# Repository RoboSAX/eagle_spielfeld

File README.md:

# eagle_spielfeld
Masterplatine des Spielfeldes

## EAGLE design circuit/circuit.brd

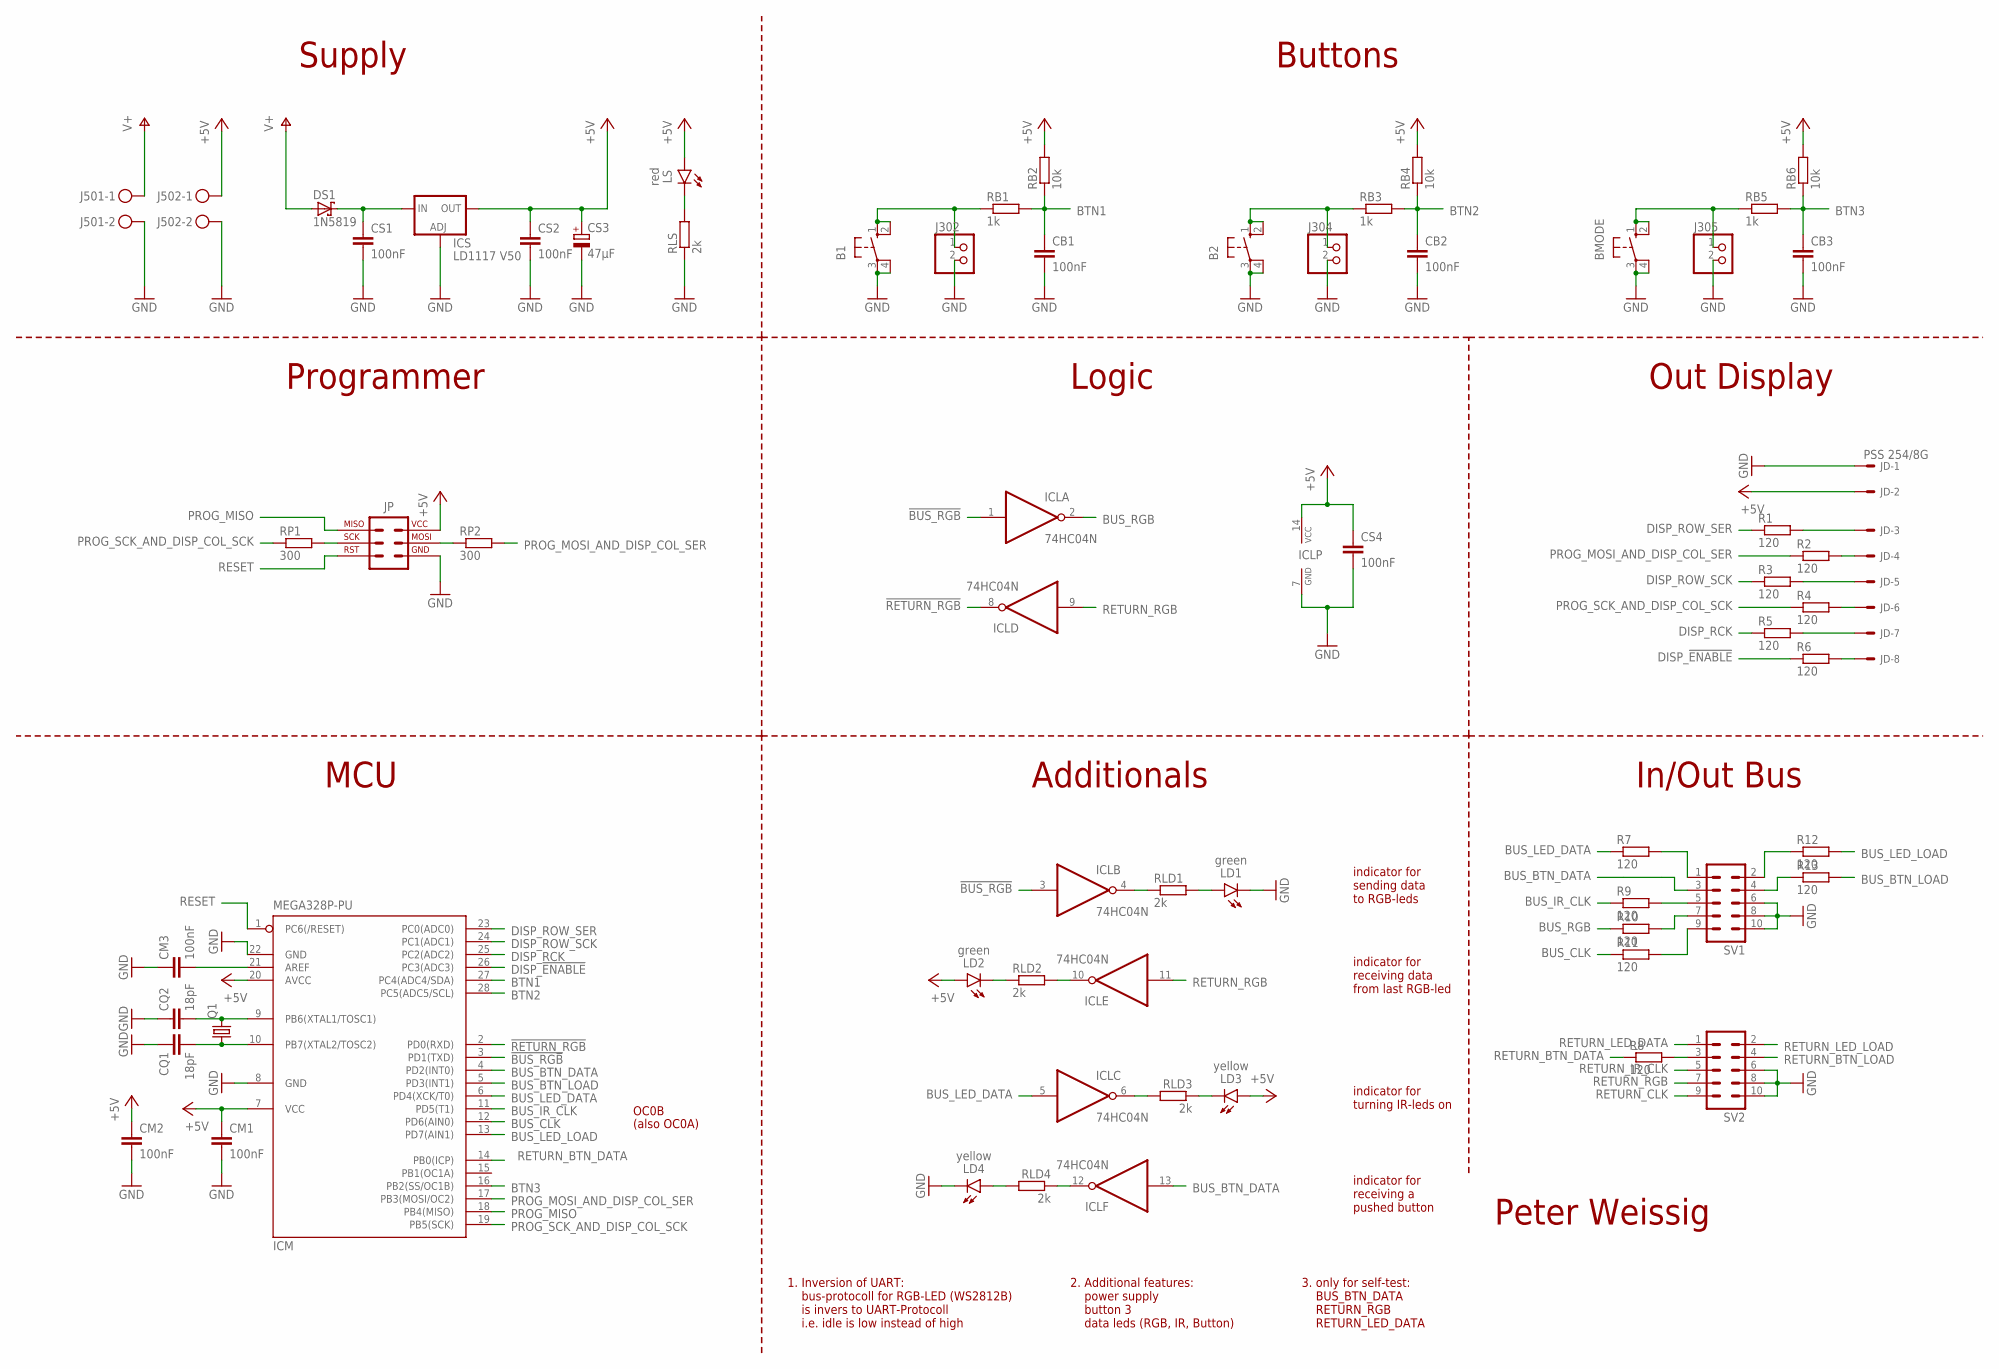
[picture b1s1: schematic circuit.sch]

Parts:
B1, B2: 10-XX; B3F-10XX
BMODE: 10-XX; B3F-10XX
CB1, CB2, CB3: 100nF; C025-025X050
CM1, CM2, CM3: 100nF; C025-025X050
CQ1, CQ2: 18pF; C025-025X050
CS1, CS2, CS4: 100nF; C025-025X050
CS3: 47µF; E2-5
DS1: 1N5819; DO41-7.6
ICL: 74HC04N; DIL14
ICM: MEGA328P-PU; DIL28-3
ICS: LD1117 V50; TO220L1
J302, J304, J305: PINHD-1X2; 1X02
J501, J502: STECKER_SPG_2
JD: PSS 254/8G; 22-23-2081
JP: STECKER_ISP_6; STECKER_WANNE_6
LD1, LD2: green; LED_3MM
LD3, LD4: yellow; LED_3MM
LS: red; LED_3MM
Q1: CRYSTALHC49U70; HC49U70
R1, R2, R3, R4, R5, R6, R7, R8, R9, R10, R11, R12, R13: 120; R1206W
RB1, RB3, RB5: 1k; 0207/10
RB2, RB4, RB6: 10k; 0207/10
RLD1, RLD2, RLD3, RLD4: 2k; 0207/10
RLS: 2k; 0207/10
RP1, RP2: 300; 0207/10
SV1, SV2: ML10

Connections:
!BUS_RGB: ICL.1 (I), ICL.3 (I), ICM.3 (PD1(TXD))
!RETURN_RGB: ICL.8 (O), ICM.2 (PD0(RXD))
+5V: CM1.1, CM2.1, CS2.1, CS3.+, CS4.1, ICL.14 (VCC), ICM.7 (VCC), ICM.20 (AVCC), ICS.2 (OUT), J502.1, JD.2, JP.2 (2_VCC), LD2.A, LD3.A, LS.A, RB2.2, RB4.2, RB6.2
BTN1: CB1.1, ICM.27 (PC4(ADC4/SDA)), RB1.2, RB2.1
BTN2: CB2.1, ICM.28 (PC5(ADC5/SCL)), RB3.2, RB4.1
BTN3: CB3.1, ICM.16 (PB2(SS/OC1B)), RB5.2, RB6.1
BUS_BTN_DATA: ICL.13 (I), ICM.4 (PD2(INT0)), SV1.3
BUS_BTN_LOAD: ICM.5 (PD3(INT1)), R13.2
BUS_CLK: ICM.12 (PD6(AIN0)), R11.1
BUS_IR_CLK: ICM.11 (PD5(T1)), R9.1
BUS_LED_DATA: ICL.5 (I), ICM.6 (PD4(XCK/T0)), R7.1
BUS_LED_LOAD: ICM.13 (PD7(AIN1)), R12.2
BUS_RGB: ICL.2 (O), R10.1
DISP_!ENABLE!: ICM.26 (PC3(ADC3)), R6.1
DISP_RCK: ICM.25 (PC2(ADC2)), R5.1
DISP_ROW_SCK: ICM.24 (PC1(ADC1)), R3.1
DISP_ROW_SER: ICM.23 (PC0(ADC0)), R1.1
GND: B1.3, B1.4 (P1), B2.3, B2.4 (P1), BMODE.3, BMODE.4 (P1), CB1.2, CB2.2, CB3.2, CM1.2, CM2.2, CM3.1, CQ1.1, CQ2.1, CS1.2, CS2.2, CS3.-, CS4.2, ICL.7 (GND), ICM.8 (GND), ICM.22 (GND), ICS.1 (ADJ), J302.2, J304.2, J305.2, J501.2, J502.2, JD.1, JP.6 (6_GND), LD1.K (C), LD4.K (C), RLS.1, SV1.6, SV1.8, SV1.10, SV2.6, SV2.8, SV2.10
unnamed: R7.2, SV1.1
unnamed: R8.2, SV2.3
unnamed: R9.2, SV1.5
unnamed: B1.1 (S), B1.2 (S1), J302.1, RB1.1
unnamed: CS1.1, DS1.C, ICS.3 (IN)
unnamed: B2.1 (S), B2.2 (S1), J304.1, RB3.1
unnamed: BMODE.1 (S), BMODE.2 (S1), J305.1, RB5.1
unnamed: CQ1.2, ICM.10 (PB7(XTAL2/TOSC2)), Q1.1
unnamed: CQ2.2, ICM.9 (PB6(XTAL1/TOSC1)), Q1.2
unnamed: LS.K (C), RLS.2
unnamed: CM3.2, ICM.21 (AREF)
unnamed: R10.2, SV1.7
unnamed: R11.2, SV1.9
unnamed: R13.1, SV1.4
unnamed: R12.1, SV1.2
unnamed: JD.3, R1.2
unnamed: JD.4, R2.2
unnamed: JD.5, R3.2
unnamed: JD.6, R4.2
unnamed: JD.7, R5.2
unnamed: JD.8, R6.2
unnamed: LD1.A, RLD1.2
unnamed: ICL.4 (O), RLD1.1
unnamed: ICL.10 (O), RLD2.2
unnamed: JP.3 (3_SCK), RP1.2
unnamed: LD2.K (C), RLD2.1
unnamed: ICL.6 (O), RLD3.2
unnamed: LD3.K (C), RLD3.1
unnamed: ICL.12 (O), RLD4.1
unnamed: LD4.A, RLD4.2
PROG_MISO: ICM.18 (PB4(MISO)), JP.1 (1_MISO)
PROG_MOSI_1: JP.4 (4_MOSI), RP2.1
PROG_MOSI_AND_DISP_COL_SER: ICM.17 (PB3(MOSI/OC2)), R2.1, RP2.2
PROG_SCK_AND_DISP_COL_SCK: ICM.19 (PB5(SCK)), R4.1, RP1.1
RESET: ICM.1 (PC6(/RESET)), JP.5 (5_RST)
RETURN_BTN_DATA: ICM.14 (PB0(ICP)), R8.1
RETURN_BTN_LOAD: SV2.4
RETURN_CLK: SV2.9
RETURN_IR_CLK: SV2.5
RETURN_LED_DATA: SV2.1
RETURN_LED_LOAD: SV2.2
RETURN_RGB: ICL.9 (I), ICL.11 (I), SV2.7
V+: DS1.A, J501.1

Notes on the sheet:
Peter Weissig
Supply
Buttons
MCU
Programmer
Out Display
In/Out Bus
Logic
1. Inversion of UART: bus-protocoll for RGB-LED (WS2812B) is invers to UART-Protocoll i.e. idle is low instead of high
3. only for self-test: BUS_BTN_DATA RETURN_RGB RETURN_LED_DATA
2. Additional features: power supply button 3 data leds (RGB, IR, Button)
(also OC0A)
OC0B
Additionals
indicator for sending data to RGB-leds
indicator for receiving data from last RGB-led
indicator for turning IR-leds on
indicator for receiving a pushed button

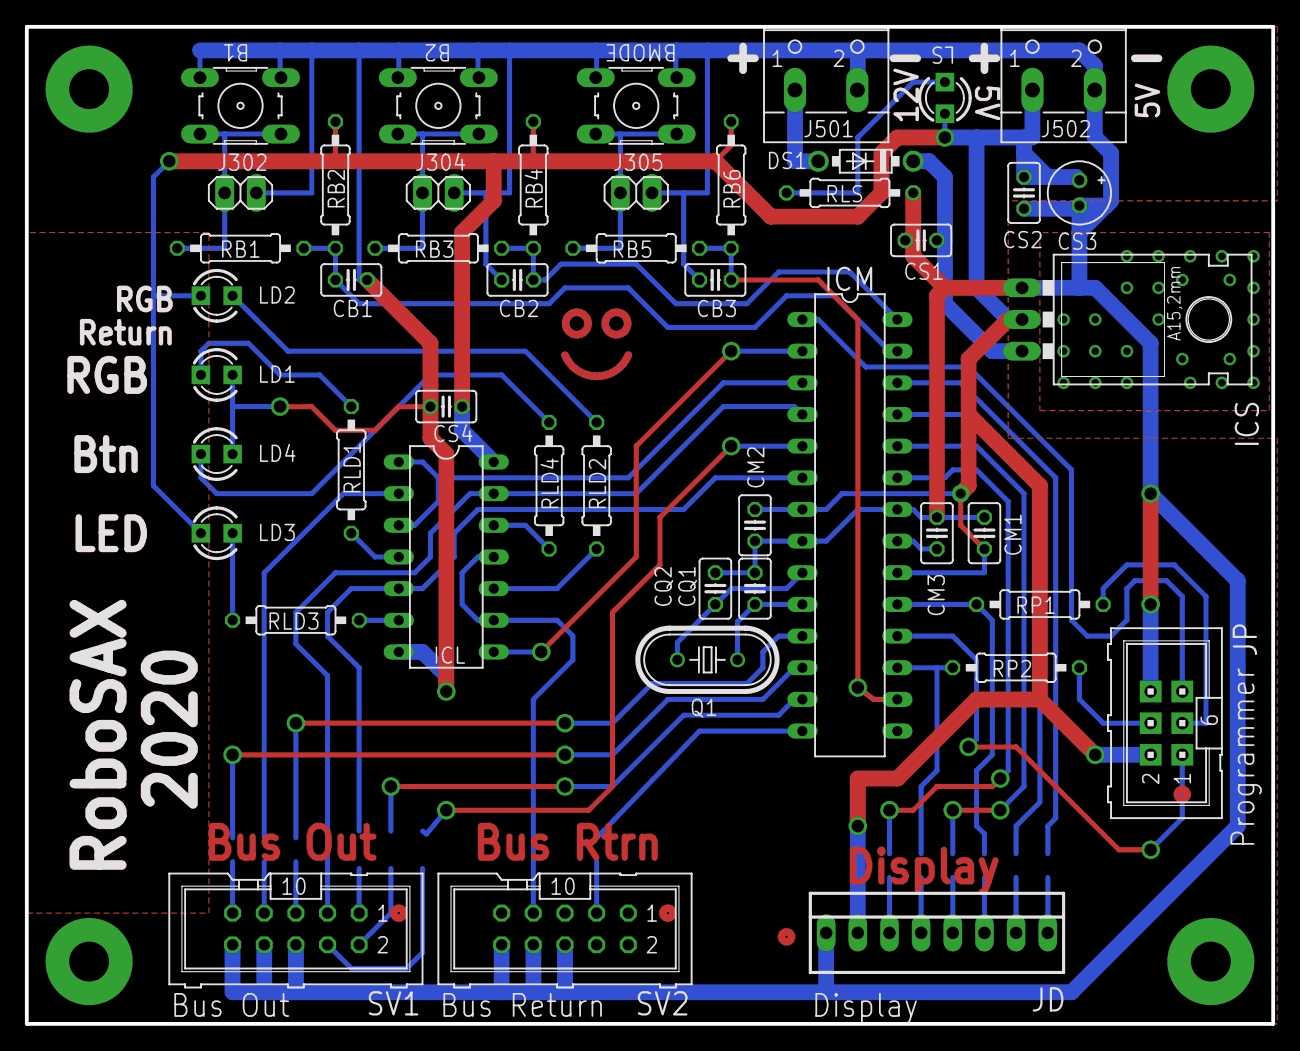
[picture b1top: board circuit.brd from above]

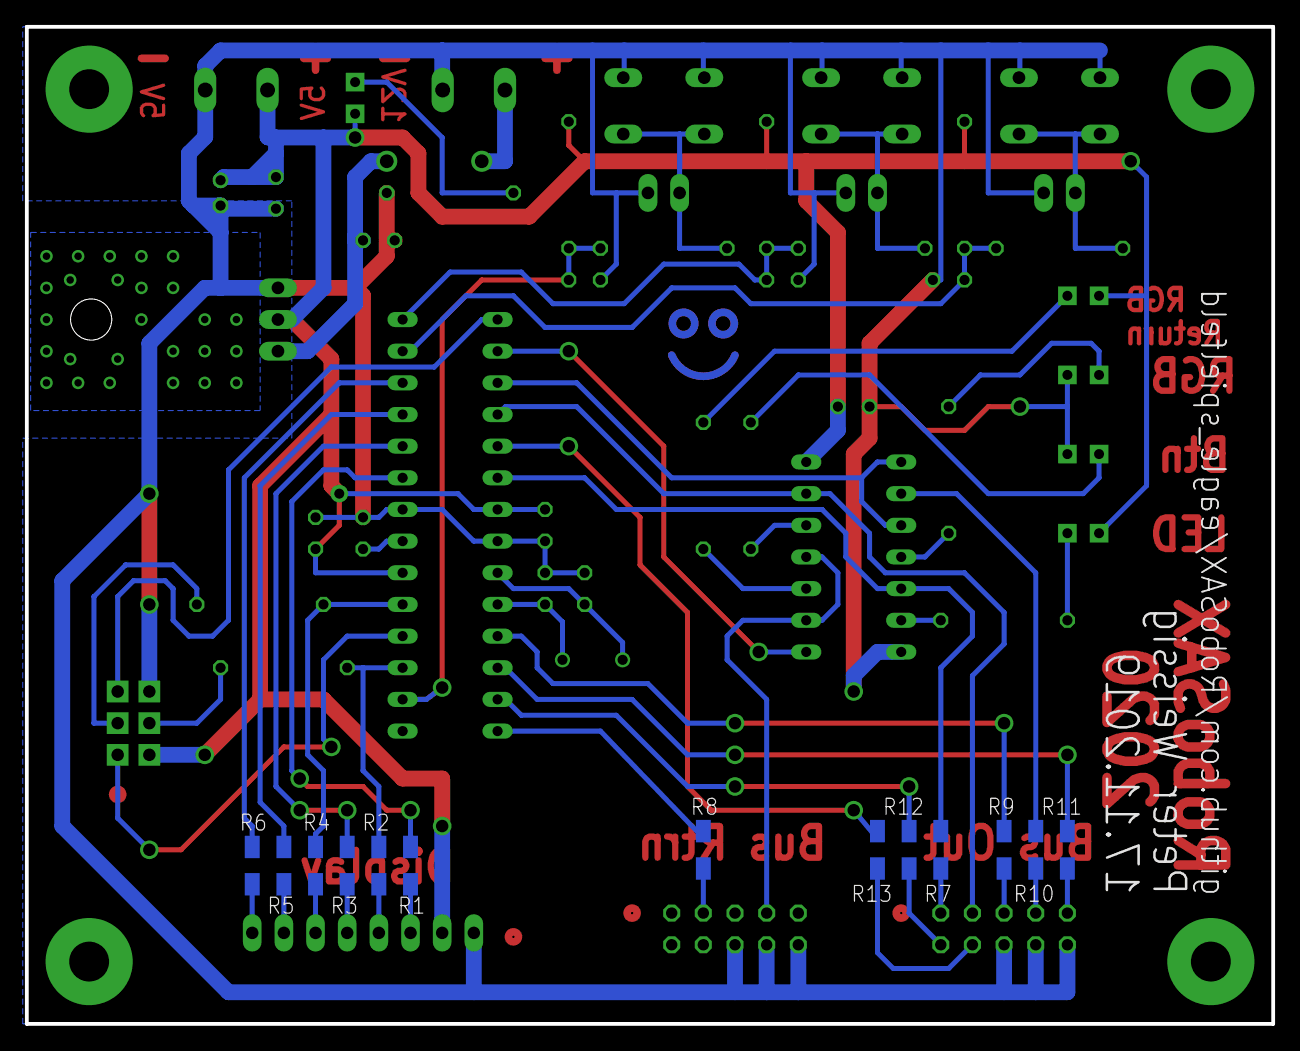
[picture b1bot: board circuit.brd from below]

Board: 2 copper layers, 100.0 x 80.0 mm, 60 parts (13 on the bottom side), 56 nets.

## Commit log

2018-05-16 initial commit (copy of eagle_licht)
2018-05-17 initial changes from elias
2018-05-18 added .gitignore
2018-05-18 updated circuit (layout needs to be done next)
2018-05-22 added exported data (circuit and layout are not done yet)
2018-05-23 Updated Layout
    Layout work in progress
2018-05-23 minor changes
2018-05-24 Layout nearly completed
2018-05-24 Layout finished
2019-04-29 updated License
2019-04-29 updated layout of circuit board + improved readability of labels + added info labels to bottom + added smiley
2019-04-29 added export for elecrow
2019-11-06 updated circuit + changed font type and size (e.g. fixed size of url) + updated cooling pad for voltage regulator + added more spacing at buttons (between pinheads and resistors) + updated part-list
2019-11-11 added Reichelt shopping cart
2019-11-17 minor fixes: + updated crystal from 16 to 20 MHz + updated package for SMD resistors (1206 instead of 0805) + fixed wrong caption (from 2019 to 2020) ==> newly exported images and elecrow files ==> u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
